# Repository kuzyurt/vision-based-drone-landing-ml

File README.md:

**[Project website and playable simulator](https://aerodock-b9t.pages.dev/)** · [Watch the film (45 s)](website/assets/hero.mp4)

# Vision-based drone landing

A drone finds a moving boat with its camera and lands on the 60 cm pad on its
deck, in wind and waves, with other boats around. Two neural networks do the
seeing; control code and the PX4 autopilot do the flying.

Everything runs in simulation. The networks were trained only in MuJoCo and
also fly in a second, realistic simulator whose graphics they never saw.
Nothing has flown on real hardware yet.

| | |
|---|---|
| Benchmark | **18 of 20** missions landed (score 79.9 / 100) |
| Networks | Search head, about 45,000 parameters; main network, about 1.55 million |
| Inputs | One 640 × 360 camera that can turn and tilt, the drone's own sensors and, if the boat sends it, its GPS position by radio |
| Outputs | Velocity, yaw rate and camera pan/tilt at 25 Hz, flown by PX4 1.16 |
| Vehicles | Holybro X500 V2 drone and the AERODOCK boat, both modelled in FreeCAD |

## How it lands

The search head looks at every camera frame and marks the boats it sees,
telling the target apart from similar and different boats. With radio, the
drone flies to the boat's position first; without it, it climbs to about 7 m
and turns on the spot until the search head finds the target. Then the main
network estimates where the pad is and how the deck is moving, and the control
code keeps the camera on the pad and the drone above it, and brings it down.
In the last few metres the camera also measures the printed pattern on the pad
directly.

[How it works, step by step](landing_training/README.md)

## Results

Each bar is one version of the design. The first was tested on 12 flights, the
others on the same 20 MuJoCo missions: five coasts, boats up to 1.5 m/s, 4 m/s
crosswind, waves, searches from 100 m and decoy boats. A landing only counts if
the drone ends up disarmed and stable on the pad.

With the search head, the final version lands every landing, wind and search
mission. It fails two
missions with waves, where it hovers just above the pad waiting for a clean
measurement until time runs out. The teacher, which sees the simulator's
ground truth, lands all 20 and marks the ceiling.

[Benchmark, evidence and viewer](benchmark/README.md)

## A second, realistic world

The [realistic simulator](tidewater-game/README.md) is a browser game with its
own ocean, sky and boats, where you can fly the drone yourself and hand it over
to the networks. They fly there without any retraining. You can
[play it in your browser](https://aerodock-b9t.pages.dev/#play) (a computer with
Chrome or Edge and a capable graphics card). In recorded sessions
with the radio switched off, the drone found the boat and landed on the pad
from 122 m away, and from 15 m with the boat behind it.

## Repository

| Folder | Content |
|---|---|
| [`landing_training/`](landing_training/README.md) | Coupled MuJoCo world, teacher, data recording and the policy |
| [`px4-mujoco-drone-simulation/`](px4-mujoco-drone-simulation/README.md) | X500 V2 drone: CAD, MuJoCo model, PX4 link |
| [`AERODOCK_MuJoCo/`](AERODOCK_MuJoCo/README.md) | AERODOCK boat: CAD, water physics, world generator |
| [`benchmark/`](benchmark/README.md) | 20-mission benchmark, five policies, all flight evidence |
| [`tidewater-game/`](tidewater-game/README.md) | Browser game with PX4, MuJoCo and the policy running locally |
| [`training_runs/`](training_runs/training_data_generation/README.md) | Training-data generation and the search-head training code |
| [`website/`](website/README.md) | Static project site |
| [`docs/`](docs/README.md) | Media, figures and background documents |
| `artifacts/`, `old/` | Frozen experiments and the previous benchmark, kept as evidence |

The benchmark pins the simulator and policy source by path and hash, so those
folders keep their names. `python -B tools/check_layout.py` verifies the pins on
a working tree that also holds the untracked experiment files in `artifacts/`.

[License](LICENSE)

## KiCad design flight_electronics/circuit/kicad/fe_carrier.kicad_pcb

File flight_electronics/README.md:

# Flight electronics

The electronics that would carry the landing policy onto the real drone, and a
simulation of them that the realistic simulator can fly through.

**Nothing here has been built or flown.** The parts are chosen, the circuit is
drawn and simulated, the code compiles and passes its tests, and the landing
policy runs through the simulated hardware. Every value comes from a data sheet,
from the existing drone model, or is marked as an assumption.

| | |
|---|---|
| Companion computer | **Orange Pi 5** (Rockchip RK3588S, 46 g), replaces the Khadas Edge2 |
| Carrier board | **FE-1 rev B**, 100 × 62 mm, 2 layers, fully routed: battery protection, 5 V / 5 A for the computer, 17 V for the camera, the radio and every connector |
| Case | 3D-printed (PETG) box with a screwed lid and vents, holds the Orange Pi 5 (with heatsink) and the carrier stacked, clamps to the X500's payload rails |
| Radio | XIAO ESP32S3 + Wio-SX1262, LoRa 868 MHz, firmware in C++ |
| Simulation | ngspice circuit models, the real firmware and protocol code, a timing model of the RK3588S |
| Realistic simulator | `tidewater-game/hardware_runner` puts this hardware between the game and the policy |

## The system

The drone, the camera and the radio module stay as bought. Three things are new:

- **Orange Pi 5 instead of the Khadas Edge2.** Same RK3588S chip, so the same
  speed. The camera sends its video only over Ethernet; the Orange Pi 5 has an
  Ethernet port, the Edge2 does not. It also has three free UARTs on its pin
  header and a plain 5 V input, so no USB adapters and no USB-PD supply are needed.
- **A 17 V supply for the camera.** The D-80Pro needs **14 to 53 V**. A 4S
  Li-ion pack is 16.8 V full and falls below 14 V under load long before it is
  empty (see [the flight simulation](#what-the-simulations-show)).
- **One carrier board** for the protection, both regulators, the radio module and
  all connectors, instead of loose modules and cables.

| Link | Wiring | Protocol |
|---|---|---|
| Camera video | GCU Ethernet → Orange Pi 5 RJ45 | RTSP sub-stream 1920 × 1080, decoded in hardware, scaled to 640 × 360 |
| Gimbal | Orange Pi 5 UART4 ↔ GCU (J4) | ALLXF GCU private protocol V2.0.6, 50 Hz, head-lock rate control |
| Autopilot | Orange Pi 5 UART1 ↔ Pixhawk 6C TELEM2 (J5) | MAVLink 2, 921 600 baud, velocity + yaw-rate setpoints |
| Boat radio | Orange Pi 5 UART3 ↔ XIAO ESP32S3 | COBS frames with CRC-16, 921 600 baud |
| Boat | SX1262 ↔ boat transmitter | LoRa SF7, 125 kHz, 32-byte beacon, 72 ms on air |

## Circuit

[Schematic as PDF](circuit/kicad/fe_carrier_schematic.pdf) · [BOM](circuit/kicad/fe_carrier_bom.csv) ·
KiCad 9 project: `circuit/kicad/fe_carrier.kicad_pro`

| Block | Parts | Why |
|---|---|---|
| Input | XT30, 10 A fuse, AOD4185 P-MOSFET, SMBJ16A, 100 µF | Reverse-polarity protection without a diode drop; clamp for spikes |
| 5 V / 5 A | TPS54560B, 6.8 µH, B560C, 3 × 47 µF | Component values are TI's own 5 V / 5 A design example |
| 17 V | TPS55340, 6.8 µH, B560C, 4 × 22 µF, 1 µH + 100 µF input filter | Above a full pack (16.8 V), 3 V above the camera minimum; the chip takes 32 V (34 V absolute), so battery-line spikes do not reach its limit |
| Radio | XIAO ESP32S3 + Wio-SX1262 on castellated pads, SS14 | The diode stops the board feeding a USB host when the XIAO is plugged in |
| Connectors | 2 × 13 header (ribbon cable to the Orange Pi 5), JST-GH to TELEM2 and the GCU, XT30 to the camera | 100 Ω series resistors on every UART line |

The pin header follows the Orange Pi 5 manual (section 3.16): 5 V on pins 2 and
4, UART1 on pins 3/5, UART4 on 16/18, UART3 on 19/21, all 3.3 V logic.

## PCB

| Top | Bottom |
|---|---|
|  |  |

Battery input on the left, the 5 V buck along the top, the 17 V boost in the
middle, the radio bottom left, the GCU and TELEM2 connectors and the camera XT30
on the right. The board has the Orange Pi 5's outline and hole pattern, with a
notch at the bottom edge: the Orange Pi sits underneath, turned by 180°, so that
its 26-pin header lies under the notch and a short ribbon cable reaches the
carrier's header J2.

- **Routed completely.** No DRC errors and no unconnected pads; the PCB matches
  the schematic exactly, and the schematic has no ERC errors. The two DRC
  warnings say only that the XT30 footprints differ from the library copy: their
  silkscreen was trimmed where it hung over the board edge.
- **Router.** `circuit/kicad/router.py` is a small grid router written for this
  board (A* on both layers, 0.1 mm grid, the design-rule clearances built in,
  rip-up and narrower retries). Every bend costs extra, and each found path is
  pulled tight into straight runs and 45° pieces, so tracks are few long
  straight segments (about 250 in all, where an unsmoothed grid route needs over
  1,300). The boost's input net is routed first, then its sensitive nets (soft
  start, frequency, feedback, compensation), short.
- **Power tracks 1.5 mm wide.** Battery, 5 V, 17 V, both switch nodes and the
  boost input run 1.5 mm wide and only neck down to 0.3 mm for the last
  fraction of a millimetre onto the TPS55340's fine-pitch pins. (Before, the
  boost input and its switch node ran 0.3 mm wide over their whole length, far
  too narrow for about 3 A.) The decoupling capacitors next to both regulators
  get their ground via first, right at the pad.
- **Ground.** Both layers carry a ground plane, stitched with vias; every plane
  island is either connected or removed.
- **Silkscreen.** Every reference and label is placed automatically where it
  touches no pad, no other text, no courtyard and stays inside the board.
- The XT30s and the XIAO stack have no KiCad 3D models, so boxes stand in for
  them in the KiCad renders; the case renders and the 3D viewer use detailed
  models of them (`mechanical/connectors.py`, `mechanical/frame.py`).

## Case

| Exploded | Lid off |
|---|---|
|  |  |

The build without the printed parts (frame, lid, rail clamps and their screws):

| Assembled | Exploded |
|---|---|
|  |  |

A printed box (106 × 68 × 46 mm; 67 g frame and 17 g lid in PETG) holds the
stack: the Orange Pi 5 on four bosses with heat-set inserts, the carrier 18 mm
above it on M2.5 standoffs, and a lid on 10 mm standoffs above the carrier. The
model is in `mechanical/frame.py` (CadQuery); print files are in `mechanical/out/`.

- **Orange Pi 5 model.** The board outline, holes and connector positions come
  from a supplied STEP model (`mechanical/models/orange_pi_5.step`). Its ports
  are boxes there; `mechanical/connectors.py` replaces them with detailed models
  in the same places (RJ45 with contacts and LEDs, stacked and vertical USB-A,
  USB-C, HDMI, audio jack, microSD with a card, pin headers).
- **Cooling.** A 35 × 35 × 10 mm aluminium heatsink with a 0.5 mm thermal pad
  sits on the RK3588S and both RAM chips, 6.5 mm below the carrier. Its fins
  run across the case, in line with vent slots in both long walls; the base
  (the top side in flight) and the lid have vents too.
- **Lid.** Four M2.5 × 6 screws into the upper standoffs. A lip locates it, and
  tongues close the connector notches down to 1 mm above each plug. It leaves
  1.5 mm above the ribbon cable, which folds over the carrier's header J2
  through the notch to the Orange Pi's header.
- **Openings** for every connector that must be reached: Ethernet (the camera),
  USB, USB-C power, HDMI, audio, the microSD card and the power key on the
  Orange Pi side; the two XT30s, both JST-GH sockets and the XIAO's USB-C on the
  carrier side, and an SMA bulkhead for the LoRa antenna with a U.FL pigtail.
- **Antenna.** An 868 MHz quarter-wave whip (86 mm) on a right-angle SMA plug
  points straight down in flight, vertical like the boat's antenna. Its tip is
  65 mm above the bottom of the landing skids and clear of the propellers, the
  legs and the camera.
- **Checked in CAD** (`mechanical/out/frame_report.json`): no part, plug or
  cable touches the frame or the lid (every port is checked with its plug,
  12 mm in front of the socket); the ribbon and the antenna lead touch no part;
  the tallest Orange Pi part is 2.2 mm below the carrier, the tallest carrier
  part 3.0 mm below the lid.
- **Mounting.** The stack is taller (46 mm) than the gap between the X500's
  plates (28 mm), and the space under the centre of the bottom plate is taken by
  the gimbal camera and the landing gear. The case therefore hangs from the
  X500's two payload rails behind the camera, with four clamps of two printed
  halves each and 2 × M3 per clamp. The kit's Intel-camera bracket sits on that
  part of the rails; this build does not use it and it comes off. Checked against
  the drone's CAD meshes: the nearest part (a rail holder) is 2.8 mm away, the
  arm screws 5.9 mm; the lid is 150 mm above the ground. The antenna, the plugs
  and their cables are checked too: the nearest drone part (the camera mount
  plate) is 5.8 mm away. The TELEM2 and GCU cables bend at the plug and run
  along the wall; straight, the TELEM2 cable would hit the gimbal camera 17 mm
  behind the back wall. The rails are 9.4 mm tubes in the CAD; measure yours and
  set `RAIL_D` before printing the clamps.
- **Drone model.** The renders, the viewer and the clearance check use the
  realistic game's detailed drone model (`tidewater-game/app/public/landing`,
  with propellers and the battery cradle), placed in the drone CAD frame by
  `mechanical/drone_model.py`. The Khadas Edge2 and the old XIAO ESP32S3 +
  SX1262 that used to sit on the top plate are gone: the Orange Pi 5 and the
  FE-1 carrier replace them. The gimbal camera is shown in colour (light ball,
  graphite yoke, blue damper plate, orange dampers, glass window; the colours
  are an assumption, no verified photographs of the D-80Pro were found).

| Print | Count | Notes |
|---|---|---|
| `mechanical/out/frame.stl` | 1 | base down, no supports; PETG or ASA, 4 walls |
| `mechanical/out/lid.stl` | 1 | plate down, no supports |
| `mechanical/out/rail_clamp_half.stl` | 8 | flat side down |

Hardware: 4 × M2.5 heat-set insert, 4 × M2.5 male-female standoff 18 mm,
4 × M2.5 male-female standoff 10 mm, 4 × M2.5 × 6 button head screw,
8 × M3 × 18 socket head screw and nut, the 35 × 35 × 10 mm heatsink with a
thermal pad, a 26-way ribbon cable of about 70 mm with two 2 × 13 IDC sockets,
an SMA bulkhead with a 100 mm U.FL pigtail.

**3D viewer.** `mechanical/viewer/` is a browser page (three.js) of the whole
assembly: the case on the drone (with the flight controller and the wiring),
the case with its parts, or the parts alone;
every part can be hidden, isolated, cut and exploded with its own factor and
direction, edges can be drawn, and views can be saved. The drone is shown at
full detail. `python -m flight_electronics.mechanical.assembly`
writes its models (`stack.glb`, `drone.glb`, `parts.json`; meshopt-compressed
when `gltfpack` is installed); serve the folder
with `python -m http.server` and open `index.html`.

## Flight controller, power and wiring

| Top deck | Underside |
|---|---|
|  |  |

The drone model had no flight controller, no ESCs and no wiring; the green
board between the plates is the Holybro PM06 power board (35 × 35 mm).
`mechanical/wiring.py` adds them, in the drone's CAD frame:

- **Flight controller.** A Holybro Pixhawk 6C (84.8 × 44 × 12.4 mm, arrow
  forward) is clamped between two printed parts over the four free M3 holes on
  the top deck's right side (x = −33 / −6 mm, y = 143 / 168 mm). The tray stands
  on 4 mm bosses, screwed to the deck with four M3 × 12 screws, washers and
  nyloc nuts under the deck, and has four corner posts with M3 heat-set inserts.
  The lid, a 3 mm frame with a window over the board and open ends over the
  connectors, is held by four M3 × 8 screws in those inserts. The board sits
  between foam pads (below) and foam strips (under the lid), so it is held
  without being hard-mounted. The 6C's port positions are approximate.
- **GPS / compass.** The black puck on the mast is a GPS receiver with a
  compass (a Holybro M10-type module, 50 mm). It sits on the mast's tray, high
  above the frame, so the compass is away from the magnetic fields of the
  battery and motor currents. Its 10-wire cable leaves the module's underside,
  runs down the mast (three cable ties) and plugs into GPS1.
- **Power.** The battery leads go from a cable gland in the cradle's side rail.
  The discharge leads (2 × 12 AWG) run down the front edge, held by two
  adhesive tie bases, to an XT60 plug on the frame's XT60 under the bottom
  plate. The frame's XT60 is wired with 14 AWG leads to the PM06's battery pads.
  The charge leads (2 × 16 AWG) go to an XT60 panel socket in a printed bracket
  on the deck's four free left-side holes. The socket faces outwards, is held
  by two M2.5 screws with nuts, and its dust cap hangs open on its strap. The
  pack charges in place; its BMS is inside it.
- **ESCs and motors.** Four 20 A ESCs lie in pairs on two printed trays. The
  trays are screwed with countersunk screws into the bottom plate's free holes,
  with nuts underneath, and each ESC is held by two cable ties through slots in
  its tray. Each ESC's power leads and signal wire are soldered to its pads on
  the PM06, in the same order as on the ESC, so the leads do not cross. The
  phase wires run inside the carbon arm tubes to the motors.
- **Camera interface.** The D-80Pro's GCU (a separate box in the set; its
  size is assumed) sits on the rear face of the camera pylon, strapped through
  the pylon's two windows. Ethernet (tied under the rail holder), 17 V (XT30)
  and the control cable come from the FE-1 case. The gimbal lead goes round the
  end of the pylon to a connector on the damper head.
- **Data and power for the electronics.** TELEM2 runs from the carrier up the
  rear corner to the 6C. The 6C's power comes from the PM06's power connector,
  and its PWM outputs go to the PM06's PWM input. The two cables run together
  under the deck and up past its rear edge. The carrier's battery input is
  soldered to the PM06's battery pads.
- **Fasteners.** Every screw goes through its part and ends in a nut or an
  insert: the tray, bracket and battery-cradle screws in nyloc nuts under the
  deck, the ESC-tray screws in nuts under the bottom plate.
- **Checked** (`mechanical/out/wiring_report.json`, tested): every wire ends on
  its terminal (plug back, solder pad, solder cup, cable gland or motor) and
  leaves it in the terminal's direction. No cable touches the drone, the case,
  a new part or another cable, apart from the last millimetres at a connector or
  inside an arm tube. Every cable keeps out of the propeller discs, and no bend
  is tighter than the cable's own diameter. Every new part clears the drone,
  except where it rests on it.
- **Weight.** About 73 g of cable, 16 cable ties and 46 g of printed PETG parts.

| Print | Count | Notes |
|---|---|---|
| `mechanical/out/fc_tray.stl` | 1 | plate down; four M3 heat-set inserts in the posts |
| `mechanical/out/fc_lid.stl` | 1 | top face down |
| `mechanical/out/charge_bracket.stl` | 1 | base down |
| `mechanical/out/esc_tray_rear.stl`, `esc_tray_front.stl` | 1 each | base down |

The realistic game's operator view shows all of this too: the case, the flight
controller, the GPS module, the power parts, the cables and the camera in colour
(`tidewater-game/app/tools/flight_electronics_parts.py` writes them into
`detail/detail.json`), and it hides the Khadas Edge2, the old XIAO, the
Intel-camera bracket and the grey camera meshes. The drone camera the policy
sees still renders the scene it was trained on, and the physics are unchanged:
none of these parts has mass in the simulation.

## Simulation

The simulation is a library that knows nothing about a particular simulator. A
world hands it, every 40 ms, what really exists: the rendered camera frame, the
autopilot's estimate, the gimbal angles, a boat radio packet. It returns what
the companion computer would really see, and what the autopilot and the gimbal
really execute.

```mermaid
flowchart LR
    W[World: realistic simulator, MuJoCo, or a replay] -->|frame, PX4 state, gimbal, radio packet| H
    subgraph H[flight_electronics.simulation]
      P[Power: ngspice in lockstep] --- C[Camera: RTSP latency, compression, drops]
      C --- M[PX4 link: MAVLink 2 bytes]
      M --- G[GCU: private protocol bytes, limits]
      G --- R[LoRa channel + ESP32 firmware]
      R --- T[RK3588S compute timing]
    end
    H -->|late frame, telemetry, encoder angles, decoded beacon| A[Policy]
    A -->|6 commands| H
    H -->|what PX4 and the gimbal execute| W
```

| Part | How it is simulated |
|---|---|
| Electrical | ngspice (the same SPICE engine KiCad uses). Cycle-by-cycle models of both converters; an averaged model of the whole aircraft supply solved in lockstep with the flight, every 40 ms. Brown-outs follow from the computed voltages. |
| ESP32 firmware | The firmware sources, compiled for the PC. A behavioral SX1262 answers the same SPI commands as the chip. |
| MAVLink, GCU | The companion code produces and parses the real bytes. The MAVLink encoder matches pymavlink byte for byte; the GCU code reproduces the example packets in the protocol document, CRC included. |
| Camera | 120 ms ± 15 ms network-camera latency (published figures for H.264 RTSP: 100–200 ms), JPEG-like compression, rare drops, 25 s reboot after a brown-out (assumption). |
| Compute | RK3588S timing model. The network runs on the NPU (from published RK3588 measurements of a network with the same amount of computation); the control code's times were measured here and scaled to one Cortex-A76 core. To be replaced by measurements on the board. |

### What the simulations show

| Question | Result |
|---|---|
| Is the 5 V supply clean? | 5.00 V, about 9 mV ripple; a 1.25 → 3.75 A step dips 136 mV (2.7 %). TI's targets: 25 mV and 4 %. |
| Does the camera supply hold? | 17.2 V from a 12 V (empty) pack, 22 mV ripple; a 1 → 2 A step dips 0.52 V (3 %). Soft start through the SS pin, 3.5 A peak switch current (limit 5.25 A). |
| Camera straight on the battery? | **It switches off after 13.5 minutes with 61 % charge left.** On the 17 V boost it stays on for the whole flight. |
| Battery-line spike, 8 V for 50 µs | The boost input reaches 27 V, below the TPS55340's 32 V rating. Rev A's TPS61288 (20 V absolute maximum) would have failed, which is why rev B changed the chip. |
| Does 25 Hz fit on the RK3588S? | Yes with the C++ marker kernel and the network on the NPU: about 18 ms while searching, 22 ms while tracking the pad, 47 ms for the first registration of the pad (one tick late). In pure Python the first registration takes about 275 ms. |

| 5 V buck | 17 V boost |
|---|---|
|  |  |

| Input spike | Decision latency |
|---|---|
|  |  |

All numbers: [`media/simulation_results.json`](media/simulation_results.json).

## Benchmark with camera latency

The final policy, flown through the simulated hardware with **0.2 s camera
latency** (images arrive 240 ms old on average), over all 20 benchmark cases,
scored like the final benchmark run. These runs were made on Linux (the
benchmark adapter is pinned to Windows; `tidewater-game/hardware_runner/linux_compat.py`
replaces only the Windows-specific parts and records every deviation), so they
are working data, not benchmark evidence. Every case is in
[`media/benchmark_camera_latency.json`](media/benchmark_camera_latency.json).

| | Final run, fresh images | Through the hardware, 0.2 s latency |
|---|---|---|
| **Score** | **79.9** | **45.2** |
| Landed | 18 / 20 | 11 / 20 |
| Landing | 100 | 50 |
| Wind | 100 | 100 |
| Waves | 50 | 50 |
| Acquisition | 100 | 70 |
| Combined | 50 | 0 |
| Speed | 73.9 | 27.2 |

What the episode digests show:

- **Moving boat (1.5 m/s), both cases:** the pad stayed in the image the whole
  time, but the policy never locked on; the mission fell back after 69 s. At
  that speed the boat moves 0.36 m between a picture and its use.
- **Far visual search, 4 cases:** three ended without finding the pad (it was in
  the image about half the time at 45–100 m, never confirmed), one found it at
  82 s and ran out of time.
- **Near the deck:** in one far-radio case the drone came within 0.3 m of the pad
  and hovered there with the lock flickering until the time ran out.
- **Landings take longer:** in the 10 cases that landed both times, the median
  time grew from 58 s to 137 s, which costs most of the speed score.
- **Not repeatable at the edge:** an earlier single run of
  landing-landing-cruise-island-r0 with the same settings ended in a collision
  at 139.9 s; in this run it landed.

The policy was trained with fresh images. It needs latency in training (or a
latency-compensated controller) before this hardware can fly it.

## Run it

Python 3.10+ with numpy; ngspice as a shared library (`apt install libngspice0`,
or `ngspice.dll` from the ngspice Windows release); a C++ compiler for the
firmware (on Windows the prebuilt `firmware/prebuilt/fe_radio_bridge.dll` is
used when no compiler is found).

```powershell
python -m unittest flight_electronics.tests -v          # protocols, firmware, circuits, board
python -m flight_electronics.firmware.build_host        # firmware for the PC + its unit tests
python -m flight_electronics.tools.make_figures         # all simulations and figures
python3.12 -m flight_electronics.circuit.kicad.generate # schematic, PCB, ERC/DRC, renders (KiCad 9)
python -m flight_electronics.mechanical.frame            # case, lid, clamps, fit and clearance report (CadQuery)
python -m flight_electronics.mechanical.render           # case renders (trimesh, pyrender)
python -m flight_electronics.mechanical.wiring           # flight controller, power parts, cables, clearance report
python -m flight_electronics.mechanical.assembly         # models for the 3D viewer (mechanical/viewer/)
python tidewater-game/app/tools/flight_electronics_parts.py  # the same parts in the realistic game's operator view
```

Fly the realistic simulator through the simulated hardware (Windows, the same
setup as `benchmark.harness.tidewater_run`):

```powershell
python -B tidewater-game/hardware_runner/run.py run --name hw_try --case <case id>
python -B tidewater-game/hardware_runner/run.py run --name hw_late --case <case id> --state-of-charge 0.3 --variant camera_on_battery
python -B tidewater-game/hardware_runner/run.py smoke    # no MuJoCo/PX4: the policy and the byte paths only
```

Every episode gets a `hardware_summary.json` next to its `result.json`:
latency, late decisions, image age, battery and camera voltages, brown-outs,
radio packets. The adapter in `tidewater-game/hardware_runner/adapter.py` is the
only code that knows both sides.

The ESP32 firmware for the real board builds with ESP-IDF:
`cd firmware/esp32_radio_bridge/platform/esp32 && idf.py set-target esp32s3 build flash`.
It has not been compiled for the ESP32 in this repository's environment.

## Layout

| Path | Contents |
|---|---|
| `hardware/design.py` | Every value, its source or its assumption |
| `hardware/board.py` | Every part, footprint and connection of the carrier board |
| `circuit/kicad/` | Generated KiCad 9 project, BOM, ERC/DRC reports, the generator and router |
| `mechanical/` | Printed case, lid and rail clamps, Orange Pi 5 and connector models, flight controller and wiring, fit checks, renders, 3D viewer |
| `firmware/esp32_radio_bridge/` | Radio bridge firmware: SX1262 driver, protocol, application, ESP-IDF entry, PC build |
| `companion/` | Orange Pi 5 code: camera pipeline, MAVLink, GCU protocol, radio link, timing |
| `simulation/` | ngspice binding and circuits, device models, `hil.py` (the hardware simulation) |
| `tools/` | Figures and the system diagram |
| `tests/` | Unit tests |

## Open points

1. **Measure the battery line** on the drone (ESC braking spikes) and check that
   the 1 µH + 100 µF filter and the TPS55340's 32 V rating leave enough margin.
2. **Measure on the board**: network on the NPU (RKNN, FP16) and the control
   code with the C++ marker kernel, then replace the timing model's numbers.
3. **Check on the bench**: the GCU control-port pinout and logic level, the sign
   of the gimbal yaw, the camera's real latency on the sub-stream, the Orange Pi
   5 power draw, the payload-rail diameter.
4. **Camera latency.** The policy was trained and benchmarked with fresh frames.
   With 0.2 s of latency the score drops from 79.9 to 45.2 (see
   [benchmark](#benchmark-with-camera-latency)); train or tune with latency.
5. **Heat.** The heatsink is estimated, not measured: with air through the case
   in flight the RK3588S should stay near 65–70 °C at 8 W; standing still at
   8 W (natural convection, about 17 K/W) it would throttle. Measure the SoC
   temperature in the closed case.
6. **Check the wiring on the real parts.** The PM06's pad layout, the 6C's
   port positions and the GCU's size are approximations; adapt the cable
   lengths and the tray, lid and bracket to the parts before printing.

## Sources

- [Orange Pi 5 user manual](https://cdn.shopify.com/s/files/1/0252/6615/9704/files/OrangePi_5_RK3588S_User_Manual_v0.7.pdf): power, 26-pin header, weight
- [ALLXF D-80Pro](https://allxf.com/product/d-80pro-40x-4k-spherical-gimbal-camera/): specification sheet, user manual, GCU private protocol
- [TI TPS54560B](https://www.ti.com/lit/ds/symlink/tps54560b.pdf), [TI TPS55340](https://www.ti.com/lit/gpn/tps55340), [TI TPS61288](https://www.ti.com/lit/ds/symlink/tps61288.pdf) (rev A)
- [Seeed XIAO ESP32S3 + Wio-SX1262](https://wiki.seeedstudio.com/wio_sx1262_with_xiao_esp32s3_kit/), Semtech SX1261/2 data sheet
- [rk-bench RK3588 NPU measurements](https://github.com/anguoyang/rk-bench), [ncnn on small boards](https://github.com/nihui/ncnn-small-board)
- Drone, battery and motor data, CAD meshes: [`px4-mujoco-drone-simulation`](../px4-mujoco-drone-simulation/README.md)
- Orange Pi 5 board and connector positions: the supplied STEP model `mechanical/models/orange_pi_5.step` ("orange pi5 v3", exported from Autodesk; its author is not recorded in the file)
- 3D viewer: [three.js](https://threejs.org) r147

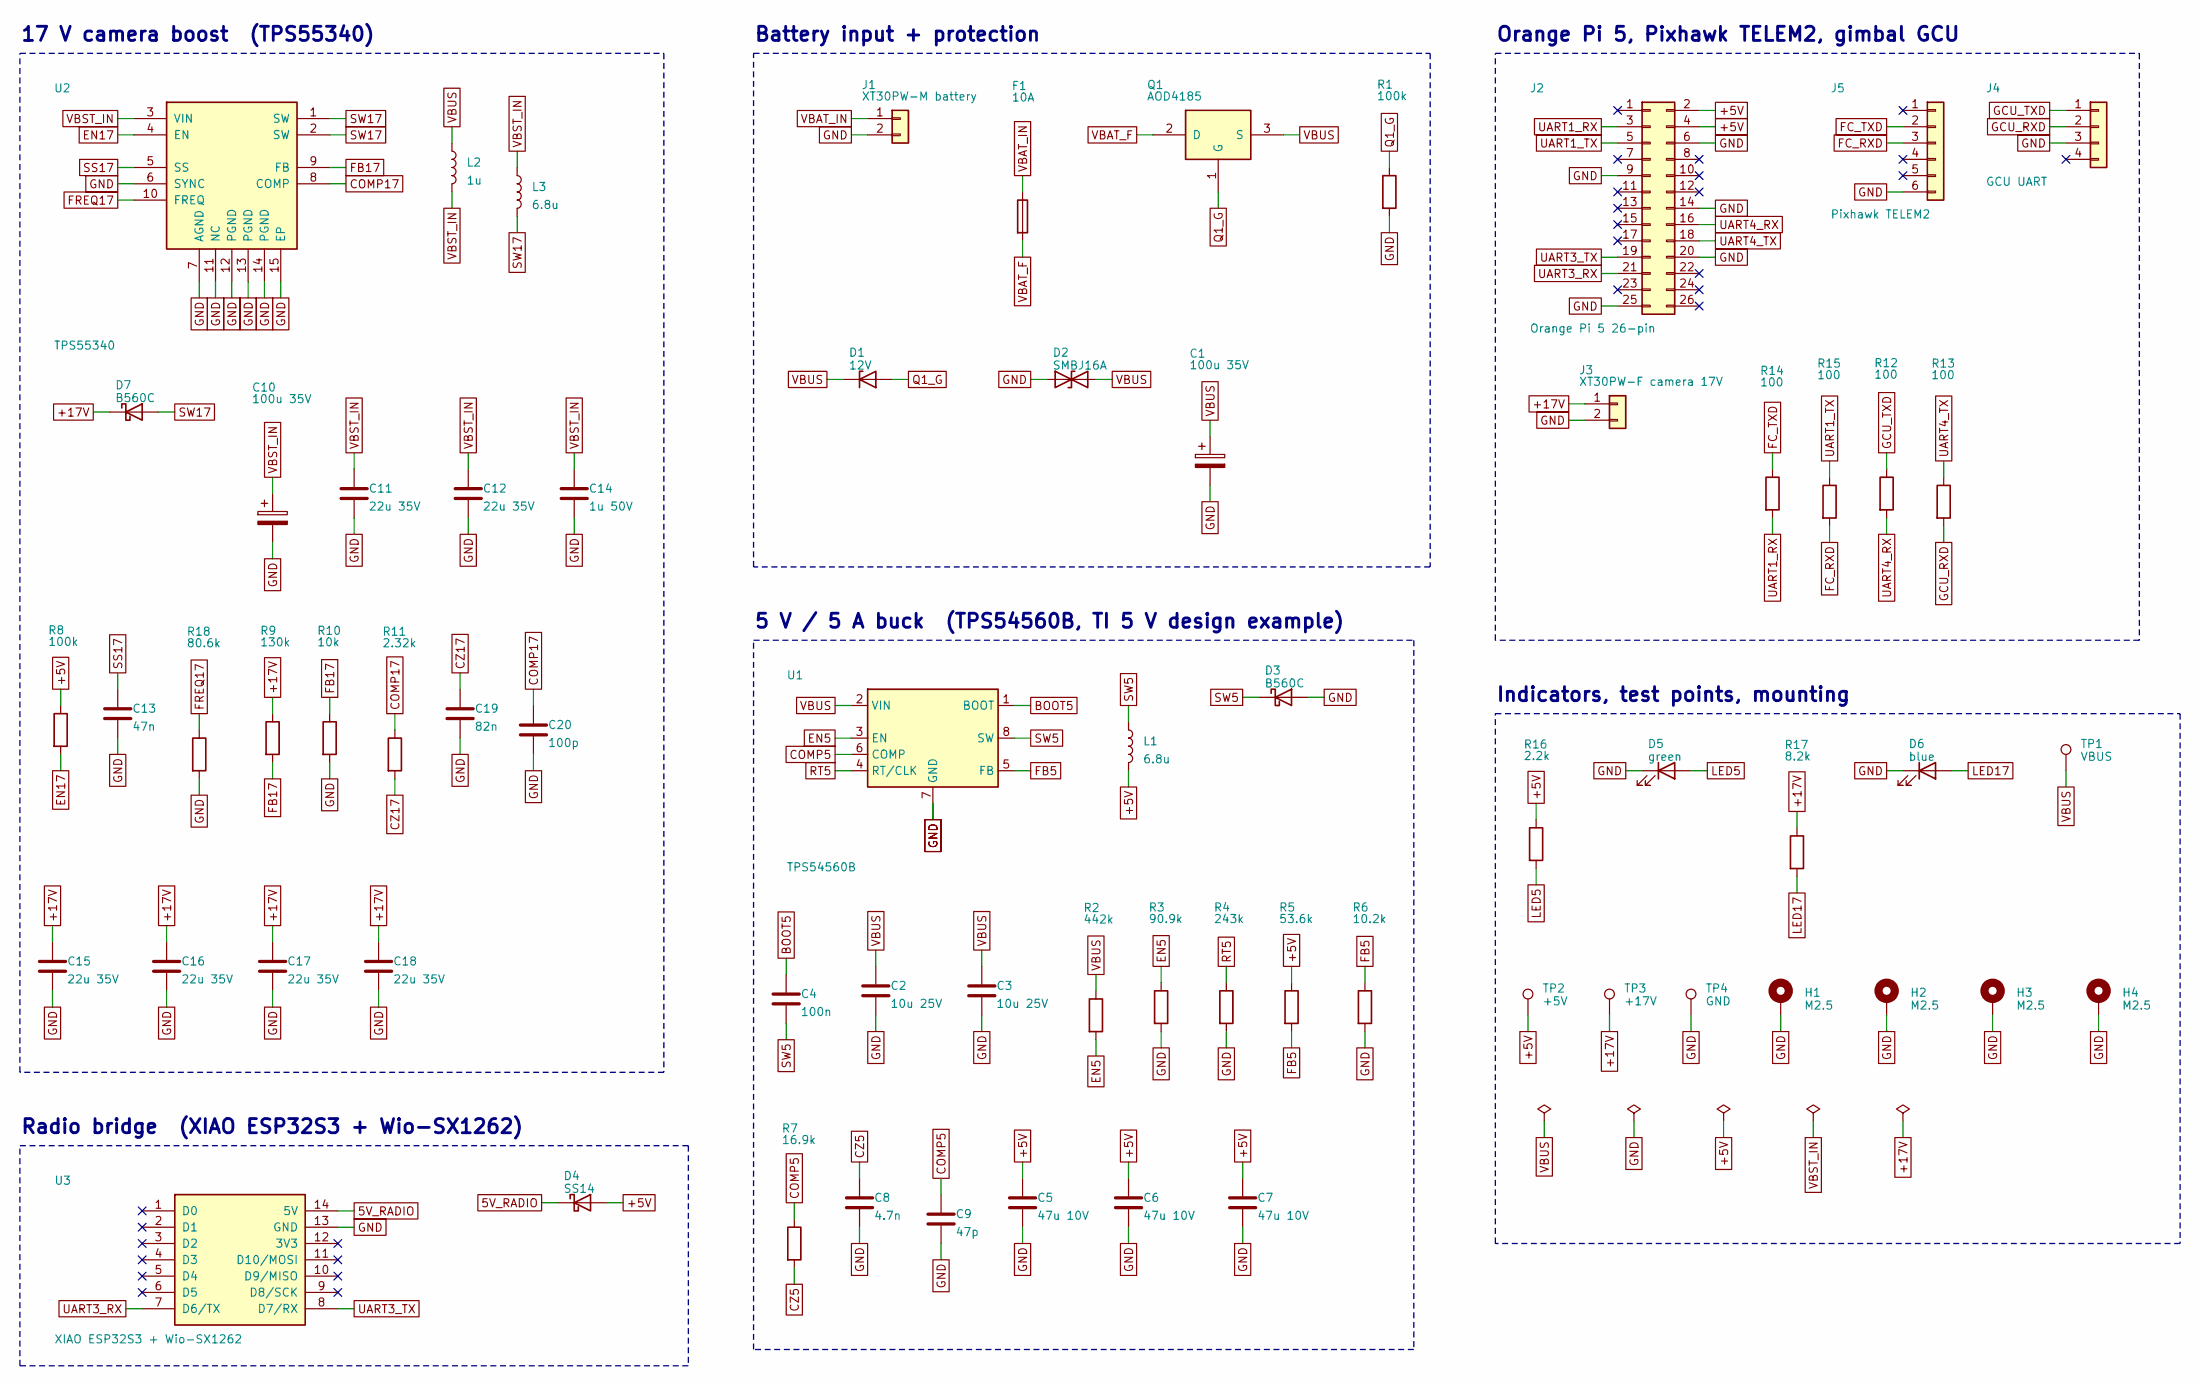
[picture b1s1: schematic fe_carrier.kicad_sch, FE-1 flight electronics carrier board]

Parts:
C1, C10: 100u 35V; CP_Elec_8x10; MPN Panasonic EEE-FK1V101P
C2, C3: 10u 25V; C_1206_3216Metric; MPN GRM31CR71E106KA12
C4: 100n; C_0603_1608Metric
C5, C6, C7: 47u 10V; C_1210_3225Metric; MPN GRM32ER71A476KE15
C8: 4.7n; C_0603_1608Metric
C9: 47p; C_0603_1608Metric
C11, C12, C15, C16, C17, C18: 22u 35V; C_1210_3225Metric; MPN GRM32EC7YA226ME05
C13: 47n; C_0603_1608Metric
C14: 1u 50V; C_0603_1608Metric
C19: 82n; C_0603_1608Metric
C20: 100p; C_0603_1608Metric
D1: 12V; D_SOD-123; MPN BZT52C12
D2: SMBJ16A; D_SMB; MPN Littelfuse SMBJ16A
D3, D7: B560C; D_SMC; MPN Diodes B560C-13-F
D4: SS14; D_SMA; MPN onsemi SS14
D5: green; LED_0603_1608Metric
D6: blue; LED_0603_1608Metric
F1: 10A; Fuse_Littelfuse-NANO2-451_453; MPN Littelfuse 0451010.MRL
H1, H2, H3, H4: M2.5; MountingHole_2.7mm_M2.5_ISO7380_Pad
J1: XT30PW-M battery; AMASS_XT30PW-M_1x02_P2.50mm_Horizontal; MPN AMASS XT30PW-M
J2: Orange Pi 5 26-pin; PinHeader_2x13_P2.54mm_Vertical; MPN Samtec TSW-113-07-G-D
J3: XT30PW-F camera 17V; AMASS_XT30PW-F_1x02_P2.50mm_Horizontal; MPN AMASS XT30PW-F
J4: GCU UART; JST_GH_SM04B-GHS-TB_1x04-1MP_P1.25mm_Horizontal; MPN JST SM04B-GHS-TB
J5: Pixhawk TELEM2; JST_GH_SM06B-GHS-TB_1x06-1MP_P1.25mm_Horizontal; MPN JST SM06B-GHS-TB
L1, L3: 6.8u; L_Coilcraft_XAL7070-XXX; MPN Coilcraft XAL7070-682MEB
L2: 1u; L_Coilcraft_XAL5030-XXX; MPN Coilcraft XAL5030-102MEB
Q1: AOD4185; TO-252-2; MPN AOS AOD4185
R1: 100k; R_0603_1608Metric; MPN RC0603FR-07100KL
R2: 442k; R_0603_1608Metric
R3: 90.9k; R_0603_1608Metric
R4: 243k; R_0603_1608Metric
R5: 53.6k; R_0603_1608Metric
R6: 10.2k; R_0603_1608Metric
R7: 16.9k; R_0603_1608Metric
R8: 100k; R_0603_1608Metric
R9: 130k; R_0603_1608Metric
R10: 10k; R_0603_1608Metric
R11: 2.32k; R_0603_1608Metric
R12, R13, R14, R15: 100; R_0603_1608Metric
R16: 2.2k; R_0603_1608Metric
R17: 8.2k; R_0603_1608Metric
R18: 80.6k; R_0603_1608Metric
TP1: VBUS; TestPoint_Pad_D1.5mm
TP2: +5V; TestPoint_Pad_D1.5mm
TP3: +17V; TestPoint_Pad_D1.5mm
TP4: GND; TestPoint_Pad_D1.5mm
U1: TPS54560B; HSOP-8-1EP_3.9x4.9mm_P1.27mm_EP2.41x3.1mm_ThermalVias; MPN TI TPS54560BDDAR
U2: TPS55340; Texas_HTSSOP-14-1EP_4.4x5mm_P0.65mm_EP3.4x5mm_Mask3.155x3.2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; MPN TI TPS55340PWPR
U3: XIAO ESP32S3 + Wio-SX1262; MCU_Seeed_ESP32C3; MPN Seeed 102010611 (kit)

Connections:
5V_RADIO: D4.1 (K), U3.14 (5V)
+5V: C5.1, C6.1, C7.1, D4.2 (A), J2.2, J2.4, L1.2, R5.1, R8.1, R16.1, TP2.1
+17V: C15.1, C16.1, C17.1, C18.1, D7.1 (K), J3.1, R9.1, R17.1, TP3.1
BOOT5: C4.1, U1.1 (BOOT)
COMP5: C9.1, R7.1, U1.6 (COMP)
COMP17: C20.1, R11.1, U2.8 (COMP)
CZ5: C8.1, R7.2
CZ17: C19.1, R11.2
EN5: R2.2, R3.1, U1.3 (EN)
EN17: R8.2, U2.4 (EN)
FB5: R5.2, R6.1, U1.5 (FB)
FB17: R9.2, R10.1, U2.9 (FB)
FC_RXD: J5.3, R15.2
FC_TXD: J5.2, R14.1
FREQ17: R18.1, U2.10 (FREQ)
GCU_RXD: J4.2, R13.2
GCU_TXD: J4.1, R12.1
GND: C1.2, C2.2, C3.2, C5.2, C6.2, C7.2, C8.2, C9.2, C10.2, C11.2, C12.2, C13.2, C14.2, C15.2, C16.2, C17.2, C18.2, C19.2, C20.2, D2.1 (A1), D3.2 (A), D5.1 (K), D6.1 (K), H1.1, H2.1, H3.1, H4.1, J1.2, J2.6, J2.9, J2.14, J2.20, J2.25, J3.2, J4.3, J5.6, R1.2, R3.2, R4.2, R6.2, R10.2, R18.2, TP4.1, U1.7 (GND), U1.9 (GND), U2.6 (SYNC), U2.7 (AGND), U2.11 (NC), U2.12 (PGND), U2.13 (PGND), U2.14 (PGND), U2.15 (EP), U3.13 (GND)
LED5: D5.2 (A), R16.2
LED17: D6.2 (A), R17.2
Q1_G: D1.2 (A), Q1.1 (G), R1.1
RT5: R4.1, U1.4 (RT/CLK)
SS17: C13.1, U2.5 (SS)
SW5: C4.2, D3.1 (K), L1.1, U1.8 (SW)
SW17: D7.2 (A), L3.2, U2.1 (SW), U2.2 (SW)
UART1_RX: J2.3, R14.2
UART1_TX: J2.5, R15.1
UART3_RX: J2.21, U3.7 (D6/TX)
UART3_TX: J2.19, U3.8 (D7/RX)
UART4_RX: J2.16, R12.2
UART4_TX: J2.18, R13.1
VBAT_F: F1.2, Q1.2 (D)
VBAT_IN: F1.1, J1.1
VBST_IN: C10.1, C11.1, C12.1, C14.1, L2.2, L3.1, U2.3 (VIN)
VBUS: C1.1, C2.1, C3.1, D1.1 (K), D2.2 (A2), L2.1, Q1.3 (S), R2.1, TP1.1, U1.2 (VIN)

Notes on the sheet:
17 V camera boost (TPS55340)
Radio bridge (XIAO ESP32S3 + Wio-SX1262)
Battery input + protection
5 V / 5 A buck (TPS54560B, TI 5 V design example)
Orange Pi 5, Pixhawk TELEM2, gimbal GCU
Indicators, test points, mounting

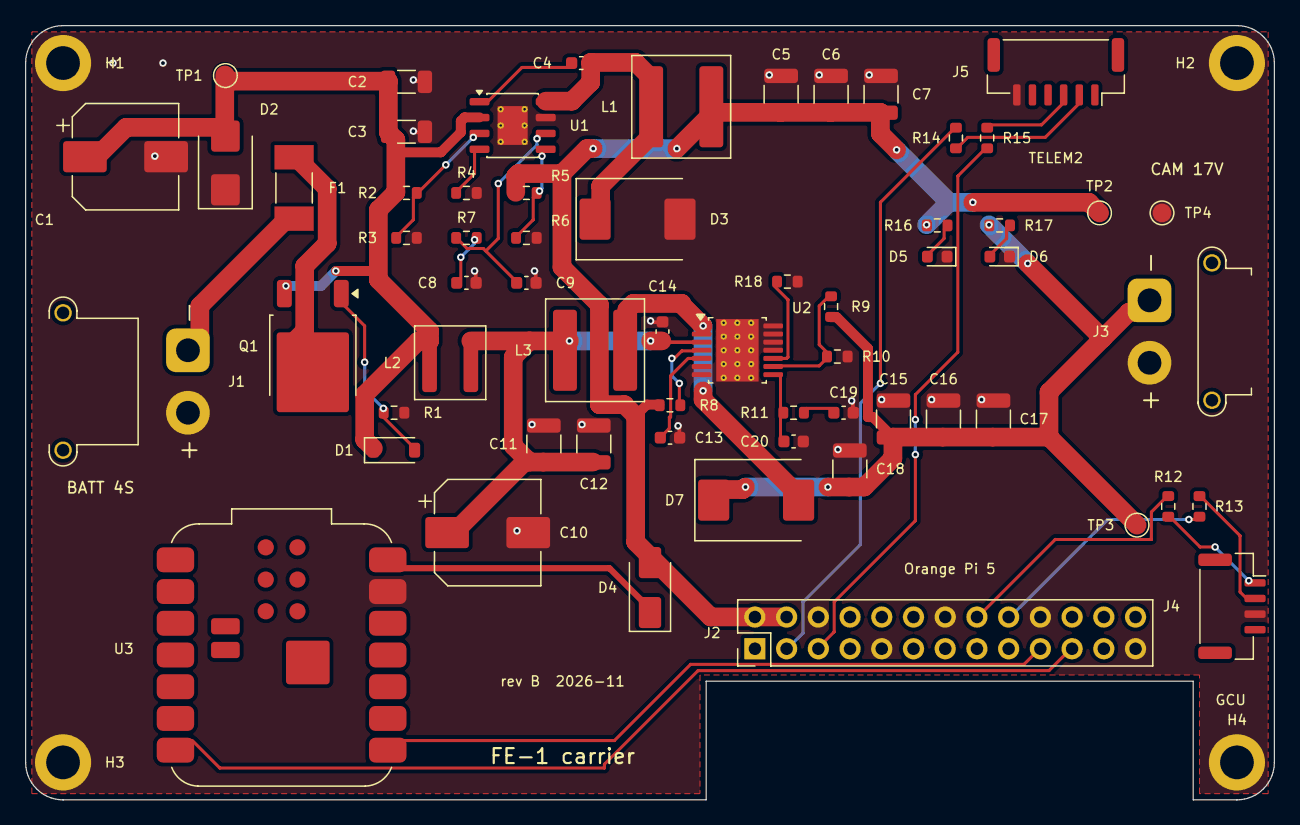
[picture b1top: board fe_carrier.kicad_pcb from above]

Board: 2 copper layers, 100.0 x 62.0 mm, 66 parts (0 on the bottom side), 35 nets.

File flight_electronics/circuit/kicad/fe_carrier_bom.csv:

refs,qty,value,footprint,mpn
"C1, C10",2,100u 35V,CP_Elec_8x10,Panasonic EEE-FK1V101P
"C11, C12, C15, C16, C17, C18",6,22u 35V,C_1210_3225Metric,GRM32EC7YA226ME05
C13,1,47n,C_0603_1608Metric,
C14,1,1u 50V,C_0603_1608Metric,
C19,1,82n,C_0603_1608Metric,
"C2, C3",2,10u 25V,C_1206_3216Metric,GRM31CR71E106KA12
C20,1,100p,C_0603_1608Metric,
C4,1,100n,C_0603_1608Metric,
"C5, C6, C7",3,47u 10V,C_1210_3225Metric,GRM32ER71A476KE15
C8,1,4.7n,C_0603_1608Metric,
C9,1,47p,C_0603_1608Metric,
D1,1,12V,D_SOD-123,BZT52C12
D2,1,SMBJ16A,D_SMB,Littelfuse SMBJ16A
"D3, D7",2,B560C,D_SMC,Diodes B560C-13-F
D4,1,SS14,D_SMA,onsemi SS14
D5,1,green,LED_0603_1608Metric,
D6,1,blue,LED_0603_1608Metric,
F1,1,10A,Fuse_Littelfuse-NANO2-451_453,Littelfuse 0451010.MRL
J1,1,XT30PW-M battery,AMASS_XT30PW-M_1x02_P2.50mm_Horizontal,AMASS XT30PW-M
J2,1,Orange Pi 5 26-pin,PinHeader_2x13_P2.54mm_Vertical,Samtec TSW-113-07-G-D
J3,1,XT30PW-F camera 17V,AMASS_XT30PW-F_1x02_P2.50mm_Horizontal,AMASS XT30PW-F
J4,1,GCU UART,JST_GH_SM04B-GHS-TB_1x04-1MP_P1.25mm_Horizontal,JST SM04B-GHS-TB
J5,1,Pixhawk TELEM2,JST_GH_SM06B-GHS-TB_1x06-1MP_P1.25mm_Horizontal,JST SM06B-GHS-TB
"L1, L3",2,6.8u,L_Coilcraft_XAL7070-XXX,Coilcraft XAL7070-682MEB
L2,1,1u,L_Coilcraft_XAL5030-XXX,Coilcraft XAL5030-102MEB
Q1,1,AOD4185,TO-252-2,AOS AOD4185
R1,1,100k,R_0603_1608Metric,RC0603FR-07100KL
R10,1,10k,R_0603_1608Metric,
R11,1,2.32k,R_0603_1608Metric,
"R12, R13, R14, R15",4,100,R_0603_1608Metric,
R16,1,2.2k,R_0603_1608Metric,
R17,1,8.2k,R_0603_1608Metric,
R18,1,80.6k,R_0603_1608Metric,
R2,1,442k,R_0603_1608Metric,
R3,1,90.9k,R_0603_1608Metric,
R4,1,243k,R_0603_1608Metric,
R5,1,53.6k,R_0603_1608Metric,
R6,1,10.2k,R_0603_1608Metric,
R7,1,16.9k,R_0603_1608Metric,
R8,1,100k,R_0603_1608Metric,
R9,1,130k,R_0603_1608Metric,
U1,1,TPS54560B,HSOP-8-1EP_3.9x4.9mm_P1.27mm_EP2.41x3.1mm_ThermalVias,TI TPS54560BDDAR
U2,1,TPS55340,Texas_HTSSOP-14-1EP_4.4x5mm_P0.65mm_EP3.4x5mm_Mask3.155x3.255mm_ThermalVias,TI TPS55340PWPR
U3,1,XIAO ESP32S3 + Wio-SX1262,MCU_Seeed_ESP32C3,Seeed 102010611 (kit)
